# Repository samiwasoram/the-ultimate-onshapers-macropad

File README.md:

# THE ULTIMATE ONSHAPER'S MACROPAD

My hackpad-inspired macropad for the Hack Club Macondo event! It's designed for ultimate CAD lock in sessions during robotics build season. It has 9 Cherry MX switches, 9 blank keycaps, and a Seeed XIAO RP2040. The PCB was created in KICAD and the case was designed in Onshape. 

The controls will be:

Row 1: Line (l), Point (shift + s), 3 Point arc (a)

Row 2: Center point circle (c), Center point rectangle (r), Corner rectangle (g)

Row 3: Construction (q), Mirror (m), Dimension (d)

I USED KICAD NOT EASYEDA

#womeninstem

# Bill of Materials    

| Item | Purpose | Price (shipping + tax included) | Source | Link |
| -------- | -------- | -------- | -------- | -------- |
| ZhouWang 10 PCS Blue Switch 3 Pin 50gf Pre-Lubricated, Dustproof Clicky Switch,Suitable for clickers for 3D Prints、MX Mechanical Keyboard | To type | $6.04 | Amazon.com | (https://www.amazon.com/ZhouWang-Pre-Lubricated-Dustproof-Prints%E3%80%81MX-Mechanical/dp/B0FKB8ZVDF/ref=sr_1_22?crid=2DQ650Y2PV0OZ&dib=eyJ2IjoiMSJ9.QRpviTOJD4a_sUXnnBHJgwAgc-lsiRiWTLZaLXMgaGouMSWtOaEYXBYZhcl-Qst1Y_x9IZjm5Sr8TmhR6Gpe5oGSP4VxGGUOUfuTvGOUV2P2dawM5bQbswkVcaRqBUTx74QX41sc7i7sQ5ROyiLt0CCInLGXfVlDndo4F1y5vHi2-4ZwSFbYYhv_L3qq3kmCIuyXcd1Mv6-DEPHpwW7MHQpBXpR9PQFeSbcTlulC6DM.agYltQE50_x8tqKPCNN1d13LCnVC4WM-8gNYtkjczaY&dib_tag=se&keywords=key%2Bswitches%2B10%2Bpack&qid=1780943139&sprefix=key%2Bswitches%2B10%2Bp%2Caps%2C297&sr=8-22&th=1) |
| 1N4148 Signal Diode - 10 pack | For keyboard matrix wiring | $12.28 (including shipping + tax for keycaps) | adafruit.com | (https://www.adafruit.com/product/1641?srsltid=AfmBOooHWAb6G50qkBp9dXtdPrK7C0nuo8gwnL6dp97hsUnvhFvnqvkOfvE) |
| White DSA Keycaps for MX Compatible Switches (10) | To type on | $5.95 (shipping + tax from Signal Diode) | adafruit.com | https://www.adafruit.com/product/4998?srsltid=AfmBOopmGq-VPcYnE1i7aQguwAhbul6IQhGv5Daf9sSj4xGf93vBrATtFjU |
| Seeed XIAO RP2040 | Microcontroller, for firmware | $10.99 | Amazon | https://www.amazon.com/Microcontroller-Dual-Core-MicroPython-CircuitPython-Interfaces/dp/B09NNVNW7M?th=1 |
| PCB | To be the macropad... | $6.06 | JLCPCB | https://jlcpcb.com/ |
| Total | $41.32 |  |  |  |

# JLCPCB cart

bueaitiful

# onshape link
https://cad.onshape.com/documents/d1f1103988d98335aa19ccdd/w/8bd042f83310a34c120b1a0e/e/0e2c7061372b8c3f71e3cb36 

# schematics

# kool images

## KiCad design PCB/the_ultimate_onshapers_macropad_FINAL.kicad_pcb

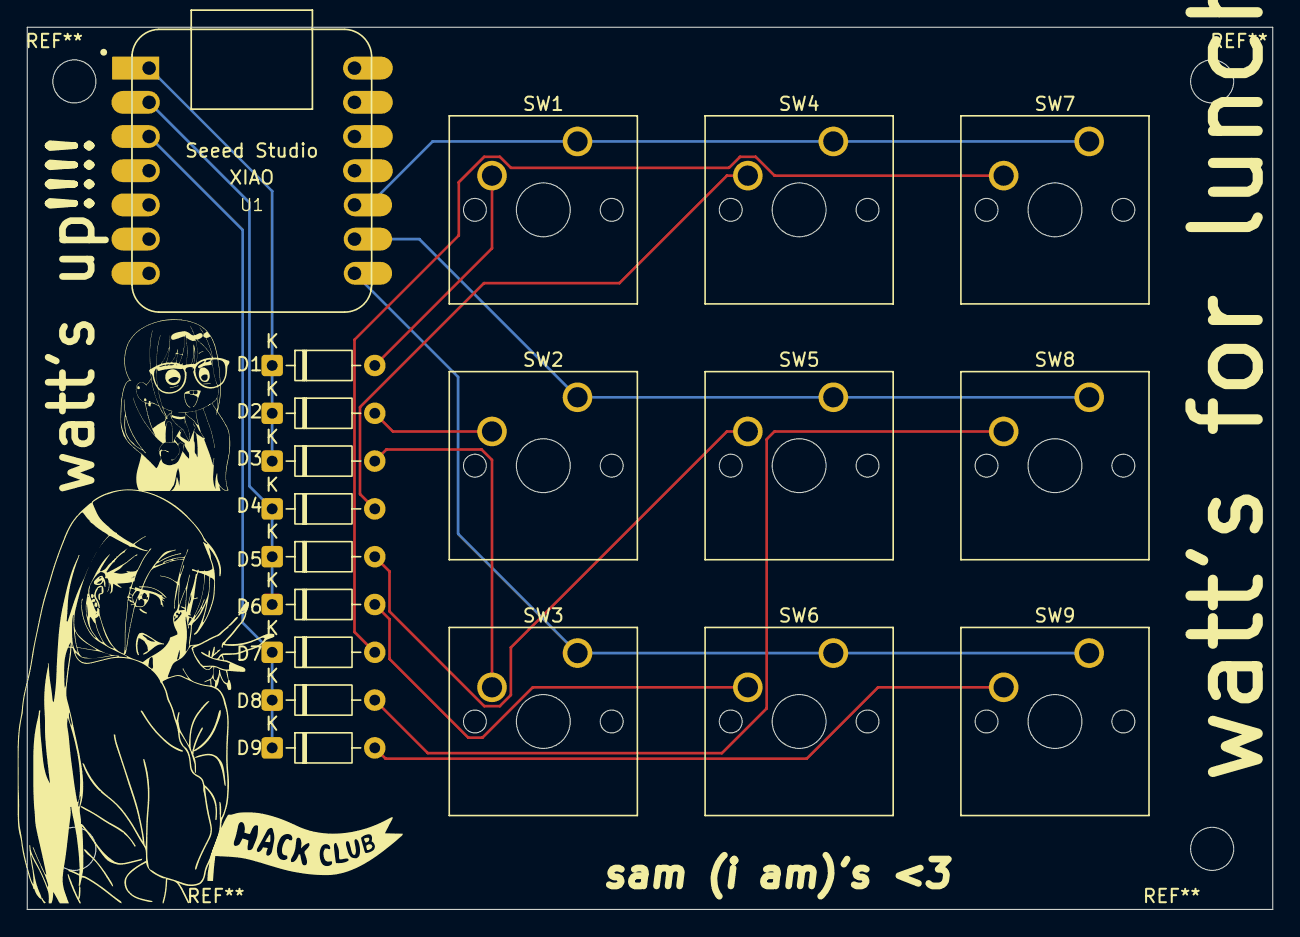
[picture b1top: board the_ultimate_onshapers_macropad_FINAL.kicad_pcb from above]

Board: 2 copper layers, 92.5 x 65.5 mm, 19 parts (0 on the bottom side), 15 nets.

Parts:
D1, D2, D3, D4, D5, D6, D7, D8, D9: 1N914; D_DO-35_SOD27_P7.62mm_Horizontal
SW1, SW2, SW3, SW4, SW5, SW6, SW7, SW8, SW9: SW_Push; SW_Cherry_MX_1.00u_PCB
U1: MOUDLE-SEEEDUINO-XIAO; XIAO-Generic-Hybrid-14P-2.54-21X17.8MM

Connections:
unnamed: D1.2 (A), SW1.2
unnamed: D2.2 (A), SW2.2
unnamed: D3.2 (A), SW3.2
unnamed: D4.2 (A), SW4.2
unnamed: D5.2 (A), SW5.2
unnamed: D6.2 (A), SW6.2
unnamed: D7.2 (A), SW7.2
unnamed: D8.2 (A), SW8.2
unnamed: D9.2 (A), SW9.2
column 0: SW1.1, SW4.1, SW7.1, U1.10 (PA5_A9_D9_MISO)
column 1: SW2.1, SW5.1, SW8.1, U1.9 (PA7_A8_D8_SCK)
column 2: SW3.1, SW6.1, SW9.1, U1.8 (PB09_A7_D7_RX)
row 0: D1.1 (K), D2.1 (K), D3.1 (K), U1.1 (PA02_A0_D0)
row 1: D4.1 (K), D5.1 (K), D6.1 (K), U1.2 (PA4_A1_D1)
row 2: D7.1 (K), D8.1 (K), D9.1 (K), U1.3 (PA10_A2_D2)
